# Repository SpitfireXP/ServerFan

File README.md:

- Belüftung eines Serverschranks mit Lüftern die noch rumlagen
- Display zur Anzeige von Temperaturen und Lüfterstufe
- Encoder zum Einstellen der Solltemparatur
- 3D-Druck gehäuse um es in den Schrank zu verbauen (In Arbeit)

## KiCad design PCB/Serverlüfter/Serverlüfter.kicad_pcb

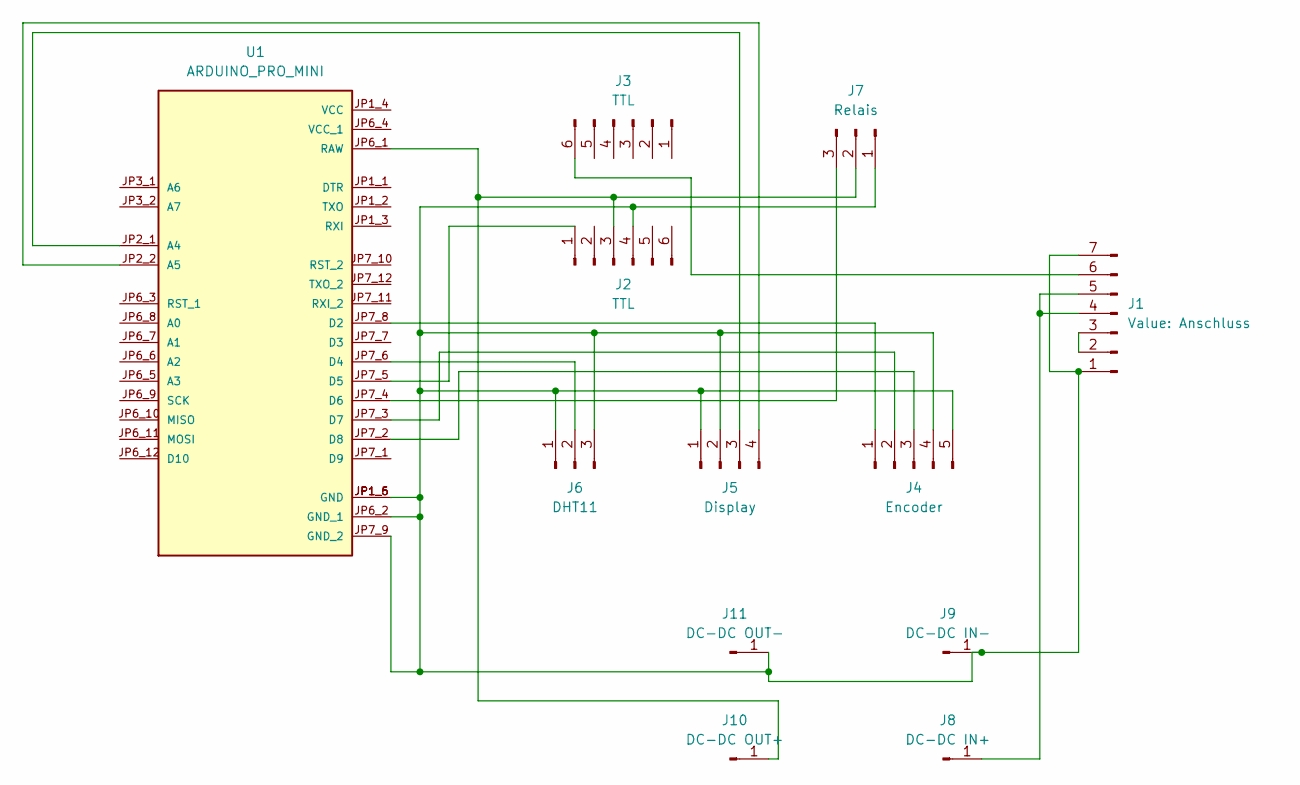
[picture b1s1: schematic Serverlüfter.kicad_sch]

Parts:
J1: Anschluss; PinHeader_1x07_P2.54mm_Vertical
J2, J3: TTL; PinHeader_1x06_P2.54mm_Vertical
J4: Encoder; PinHeader_1x05_P2.54mm_Vertical
J5: Display; PinHeader_1x04_P2.54mm_Vertical
J6: DHT11; PinHeader_1x03_P2.54mm_Vertical
J7: Relais; PinHeader_1x03_P2.54mm_Vertical
J8: DC-DC IN+; PinHeader_1x01_P2.54mm_Vertical
J9: DC-DC IN-; PinHeader_1x01_P2.54mm_Vertical
J10: DC-DC OUT+; PinHeader_1x01_P2.54mm_Vertical
J11: DC-DC OUT-; PinHeader_1x01_P2.54mm_Vertical
U1: ARDUINO_PRO_MINI; MODULE_ARDUINO_PRO_MINI; PARTREV N/A

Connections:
unnamed: J1.1, J1.7, J2.4, J4.4, J4.5, J5.1, J5.2, J6.1, J6.3, J7.1, J9.1, J11.1, U1.JP1_5 (GND), U1.JP1_6 (GND), U1.JP6_2 (GND_1), U1.JP7_9 (GND_2)
unnamed: J1.2, J1.3
unnamed: J1.4, J1.5, J8.1
unnamed: J1.6, J3.6
unnamed: J2.1, U1.JP7_5 (D5)
unnamed: J4.1, U1.JP7_8 (D2)
unnamed: J4.2, U1.JP7_3 (D7)
unnamed: J4.3, U1.JP7_2 (D8)
unnamed: J5.3, U1.JP2_1 (A4)
unnamed: J5.4, U1.JP2_2 (A5)
unnamed: J6.2, U1.JP7_6 (D4)
unnamed: J7.3, U1.JP7_4 (D6)
unnamed: J2.3, J7.2, J10.1, U1.JP6_1 (RAW)

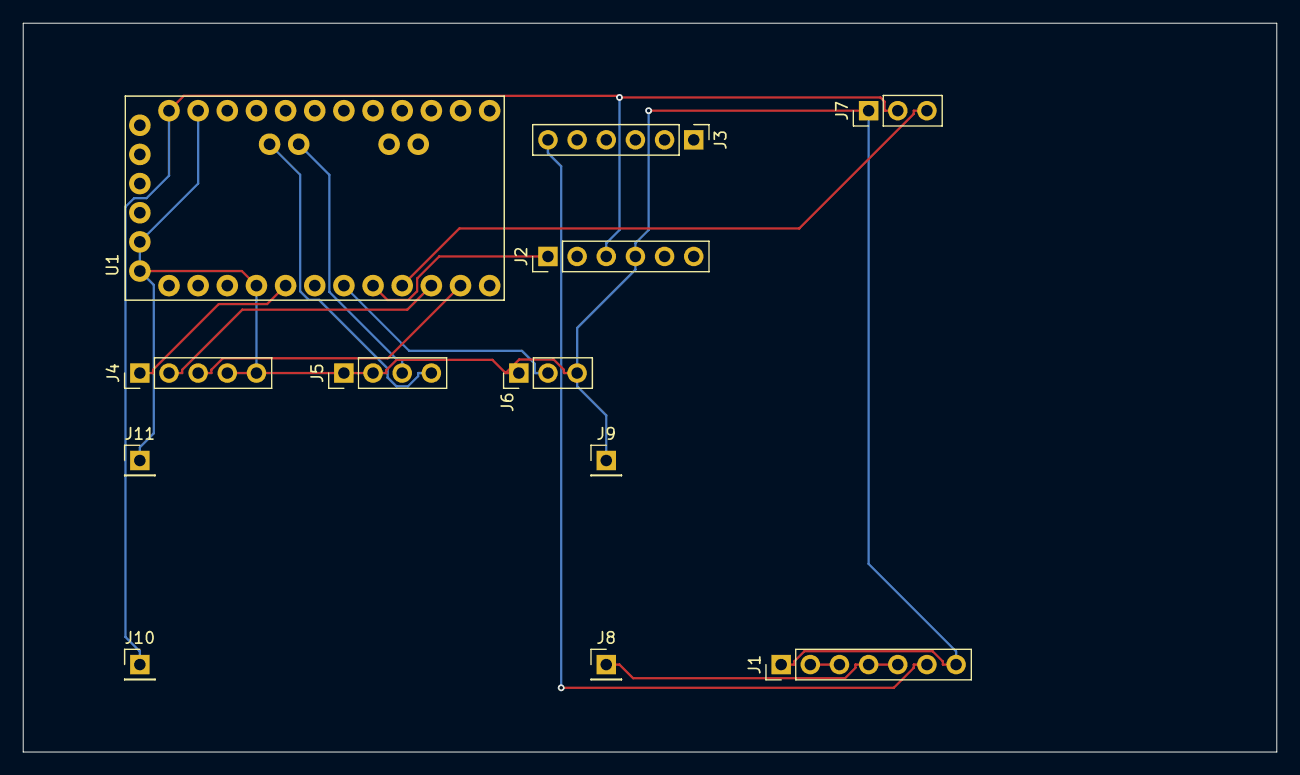
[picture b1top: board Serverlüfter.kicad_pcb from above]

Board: 2 copper layers, 109.2 x 63.5 mm, 12 parts (0 on the bottom side), 13 nets.

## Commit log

2024-10-16 init
2024-10-26 Rotary Encoder
2024-10-26 add Relay
2024-11-01 Encoder added
2024-11-02 New Encoderlib
2024-11-02 Encoder part added
2024-11-02 Testing
2024-11-02 add Button
2024-12-03 Added PCB
2024-12-03 Add PCB
2024-12-29 New Code
2024-12-29 Code Changes
2025-01-04 Richtiger Code
2025-01-04 Code
2025-01-04 PWM Signal feiner regulierend
2025-01-04 Invert PWM-Signal
2025-01-04 Codechange
2025-01-04 Kommentar
2025-01-04 Change Readme
